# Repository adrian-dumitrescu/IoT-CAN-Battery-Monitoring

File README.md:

# IoT-CAN-Battery-Monitoring

Information about the device is presented in the pCloud_Documentation.pdf file.
- [x] Arduino IDE
- [x] Based on ESP8266
- [x] IoT monitoring with Thingsboard Dashboard
- [x] CAN-BUS

## License
[MIT](https://choosealicense.com/licenses/mit/)

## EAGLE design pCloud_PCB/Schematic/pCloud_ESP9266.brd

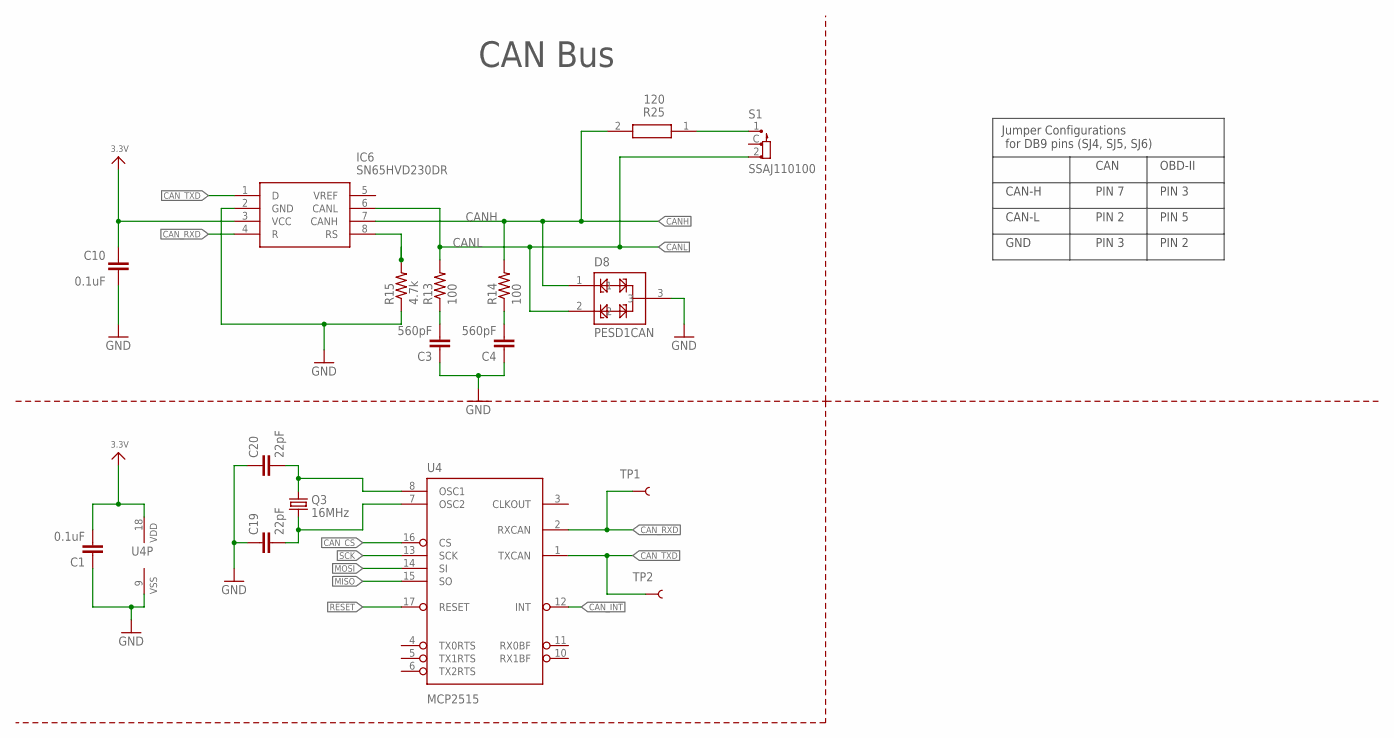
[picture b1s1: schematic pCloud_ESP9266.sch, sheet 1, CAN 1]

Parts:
C1, C10: 0.1uF; 0603
C3, C4: 560pF; 0603
C19, C20: 22pF; 0603
D8: PESD1CAN; SOT23-3
IC6: SN65HVD230DR; SOT127P600X175-8N
Q3: 16MHz; CRYSTAL-SMD-5X3
R13, R14: 100; 0603
R15: 4.7k; 0603
R25: 120; RESC1608X55N
S1: SSAJ110100; SW_SSAJ110100
TP1, TP2: TEST-POINT3X5; PAD.03X.05
U4: MCP2515; SO-18W

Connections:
3.3V: C1.2, C10.2, IC6.3 (VCC), U4.18 (VDD); also elsewhere on the board
CANH: D8.1, IC6.7 (CANH), R14.2, R25.2; also elsewhere on the board
CANL: D8.2, IC6.6 (CANL), R13.2, S1.2; also elsewhere on the board
CAN_CS: U4.16 (CS); also elsewhere on the board
CAN_INT: U4.12 (INT); also elsewhere on the board
CAN_RXD: IC6.4 (R), TP1.P$1, U4.2 (RXCAN)
CAN_TXD: IC6.1 (D), TP2.P$1, U4.1 (TXCAN)
GND: C1.1, C3.1, C4.1, C10.1, C19.1, C20.1, D8.3, IC6.2 (GND), R15.1, U4.9 (VSS); also elsewhere on the board
MISO: U4.15 (SO); also elsewhere on the board
MOSI: U4.14 (SI); also elsewhere on the board
unnamed: C3.2, R13.1
unnamed: C4.2, R14.1
unnamed: R25.1, S1.1
unnamed: IC6.8 (RS), R15.2
unnamed: C20.2, Q3.3 (2), U4.8 (OSC1)
unnamed: C19.2, Q3.1, U4.7 (OSC2)
RESET: U4.17 (RESET); also elsewhere on the board
SCK: U4.13 (SCK); also elsewhere on the board

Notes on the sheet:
CAN Bus
CAN
OBD-II
CAN-H
CAN-L
GND
PIN 5
PIN 2
PIN 3
PIN 7
Jumper Configurations for DB9 pins (SJ4, SJ5, SJ6)

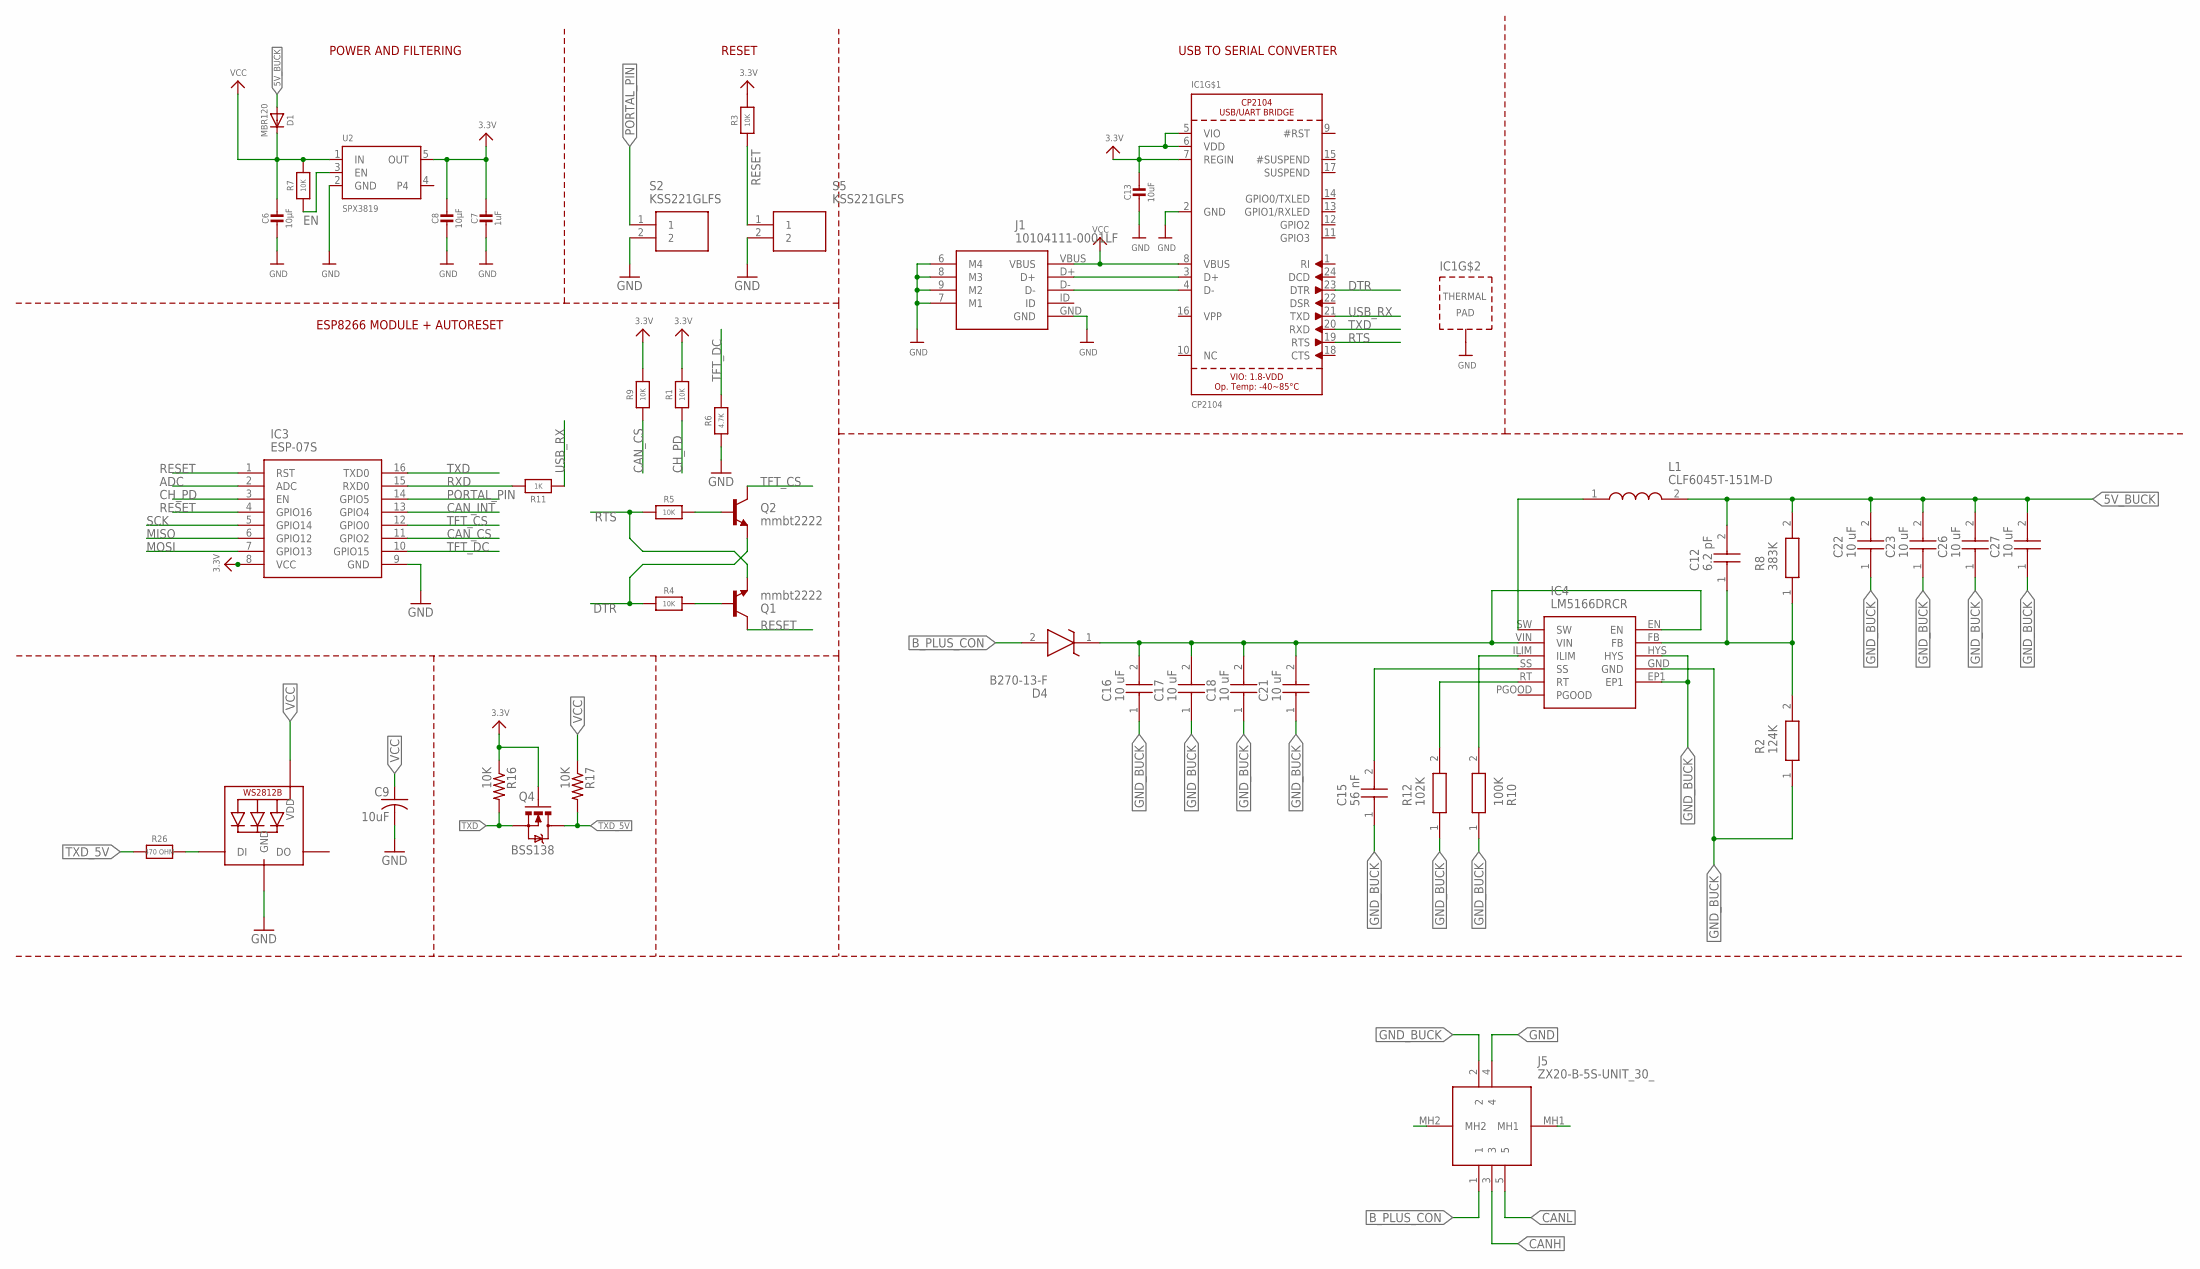
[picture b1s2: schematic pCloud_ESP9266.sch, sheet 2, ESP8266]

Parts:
C6, C8: 10µF; 0805
C7: 1uF; 0603
C9: 10uF; C0805K
C12: 6.2 pF; CAPC1005X55N
C13: 10uF; 0805
C15: 56 nF; CAPC1005X55N
C16, C17, C18, C21, C22, C23, C26, C27: 10 uF; CAPC3225X270N
D1: MBR120; SOD-123
D4: B270-13-F; DIOM5336X250N
IC1: CP2104; QFN24_4MM_SMSC
IC3: ESP-07S; ESP07S
IC4: LM5166DRCR; TPS74901DRCR
J1: 10104111-0001LF; 101041110001LF
J5: ZX20-B-5S-UNIT_30_; ZX20B5SUNIT30
L1: CLF6045T-151M-D; CLF6045T151MD
LED4: WS2812B5050; WS2812B
Q1, Q2: mmbt2222; SOT23-3
Q4: BSS138; SOT23-3
R1, R3, R4, R5, R7, R9, R16, R17: 10K; 0603
R2: 124K; RESC1005X40N
R6: 4.7K; 0603
R8: 383K; RESC1005X40N
R10: 100K; RESC1005X40N
R11: 1K; 0603
R12: 102K; RESC1005X40N
R26: 470 OHM; _0805MP
S2, S5: KSS221GLFS; KSS
U2: SPX3819; SOT23-5

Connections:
3.3V: C7.1, C8.1, C13.1, IC1.5 (VIO), IC1.6 (VDD), IC1.7 (REGIN), IC3.8 (VCC), Q4.1 (G), R1.2, R3.2, R9.2, R16.1, U2.5 (OUT); also elsewhere on the board
5V_BUCK: C12.2, C22.2 (C2), C23.2 (C2), C26.2 (C2), C27.2 (C2), D1.A, L1.2, R8.2
ADC: IC3.2 (ADC)
B_PLUS: C16.2 (C2), C17.2 (C2), C18.2 (C2), C21.2 (C2), D4.1 (K), IC4.EN, IC4.VIN
B_PLUS_CON: D4.2 (A), J5.1
CANH: J5.3; also elsewhere on the board
CANL: J5.5; also elsewhere on the board
CAN_CS: IC3.11 (GPIO2), R9.1; also elsewhere on the board
CAN_INT: IC3.13 (GPIO4); also elsewhere on the board
CH_PD: IC3.3 (EN), R1.1
DTR: IC1.23 (DTR), Q2.2 (E), R4.1
EN: R7.1, U2.3 (EN)
GND: C6.2, C7.2, C8.2, C9.2, C13.2, IC1.2 (GND), IC1.THERM (TP), IC3.9 (GND), J1.6 (M4), J1.7 (M1), J1.8 (M3), J1.9 (M2), J1.GND, J5.4, LED4.3-GND (GND), R6.1, S2.2, S5.2, U2.2 (GND); also elsewhere on the board
GND_BUCK: C15.1, C16.1 (C1), C17.1 (C1), C18.1 (C1), C21.1 (C1), C22.1 (C1), C23.1 (C1), C26.1 (C1), C27.1 (C1), IC4.EP1, IC4.GND, IC4.HYS, J5.2, R2.1, R10.1, R12.1
MISO: IC3.6 (GPIO12); also elsewhere on the board
MOSI: IC3.7 (GPIO13); also elsewhere on the board
unnamed: IC4.SW, L1.1
unnamed: IC4.ILIM, R10.2
unnamed: C12.1, IC4.FB, R2.2, R8.1
unnamed: IC1.3 (D+), J1.D+
unnamed: IC1.4 (D-), J1.D-
unnamed: Q1.1 (B), R4.2
unnamed: Q2.1 (B), R5.2
unnamed: C15.2, IC4.SS
unnamed: IC4.RT, R12.2
unnamed: LED4.4-DIN (DI), R26.2
PORTAL_PIN: IC3.14 (GPIO5), S2.1
RESET: IC3.1 (RST), IC3.4 (GPIO16), Q1.3 (C), R3.1, S5.1; also elsewhere on the board
RTS: IC1.19 (RTS), Q1.2 (E), R5.1
RXD: IC3.15 (RXD0), R11.2
SCK: IC3.5 (GPIO14); also elsewhere on the board
TFT_CS: IC3.12 (GPIO0), Q2.3 (C); also elsewhere on the board
TFT_DC: IC3.10 (GPIO15), R6.2; also elsewhere on the board
TXD: IC1.20 (RXD), IC3.16 (TXD0), Q4.2 (S), R16.2
TXD_5V: Q4.3 (D), R17.2, R26.1
USB_RX: IC1.21 (TXD), R11.1
VCC: C6.1, C9.1, D1.C, IC1.8 (VBUS), J1.VBUS, LED4.1-VDD (VDD), R7.2, R17.1, U2.1 (IN)

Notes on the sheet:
POWER AND FILTERING
RESET
USB TO SERIAL CONVERTER
ESP8266 MODULE + AUTORESET

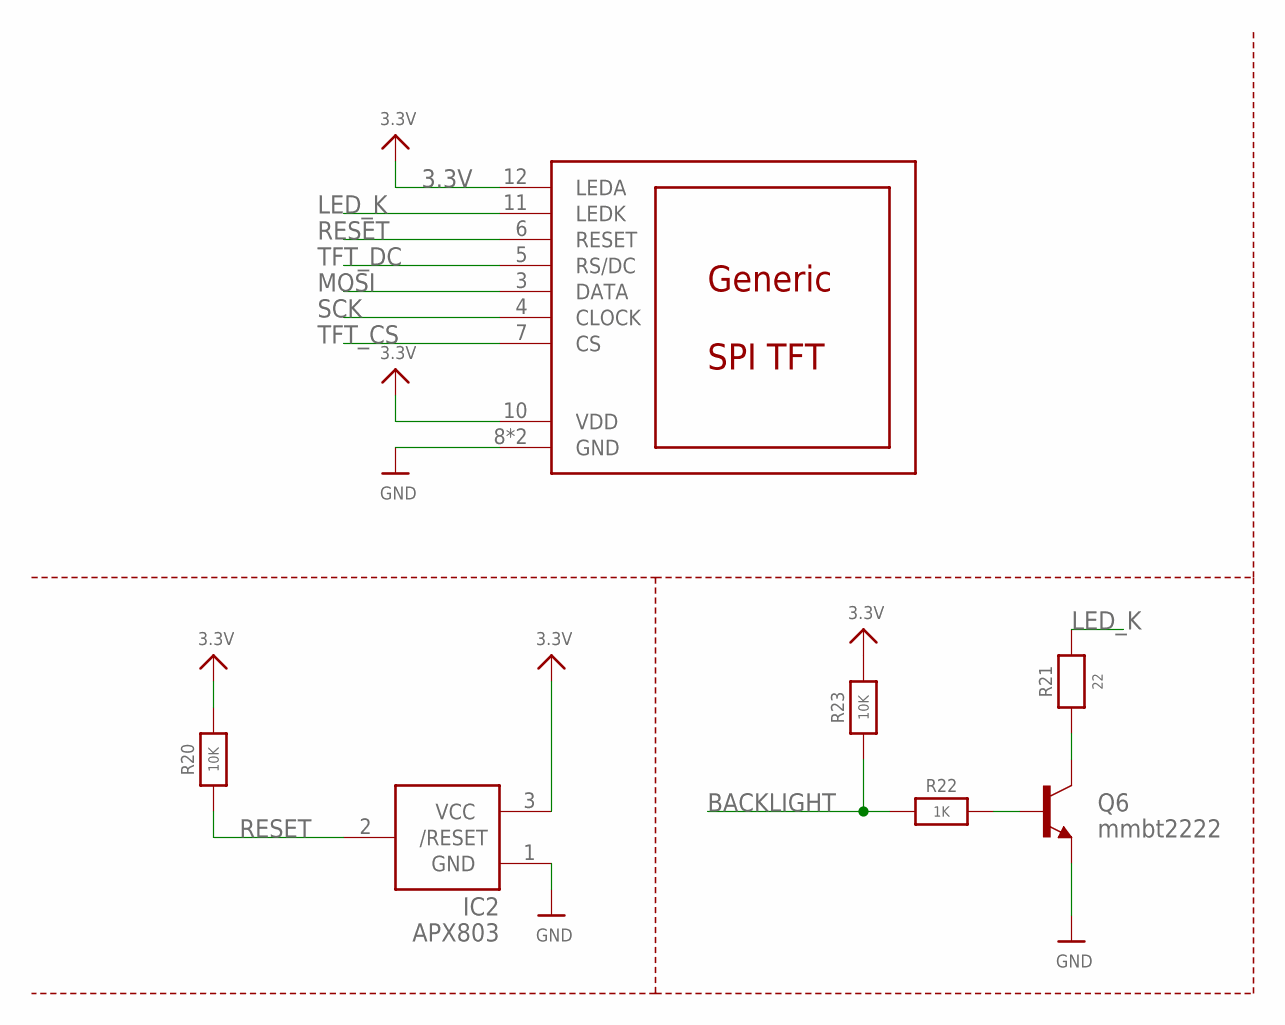
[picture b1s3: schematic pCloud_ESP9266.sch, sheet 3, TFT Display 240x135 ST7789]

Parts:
DISP1: DISP_LCD_GENERIC_SPI_1.14IN_240X135_WRAPUNDER; TFT_1.14IN_240X135_WRAPUNDER
IC2: APX803; SOT23
Q6: mmbt2222; SOT23-3
R20, R23: 10K; 0603
R21: 22; 0603
R22: 1K; 0603

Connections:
3.3V: DISP1.10 (VDD), DISP1.12 (LEDA), IC2.3 (VCC), R20.2, R23.2; also elsewhere on the board
BACKLIGHT: R22.1, R23.1
GND: DISP1.8 (GND), DISP1.13 (GND), IC2.1 (GND), Q6.2 (E); also elsewhere on the board
LED_K: DISP1.11 (LEDK), R21.2
MOSI: DISP1.3 (DATA); also elsewhere on the board
unnamed: Q6.1 (B), R22.2
unnamed: Q6.3 (C), R21.1
RESET: DISP1.6 (RESET), IC2.2 (/RESET), R20.1; also elsewhere on the board
SCK: DISP1.4 (CLOCK); also elsewhere on the board
TFT_CS: DISP1.7 (CS); also elsewhere on the board
TFT_DC: DISP1.5 (RS/DC); also elsewhere on the board

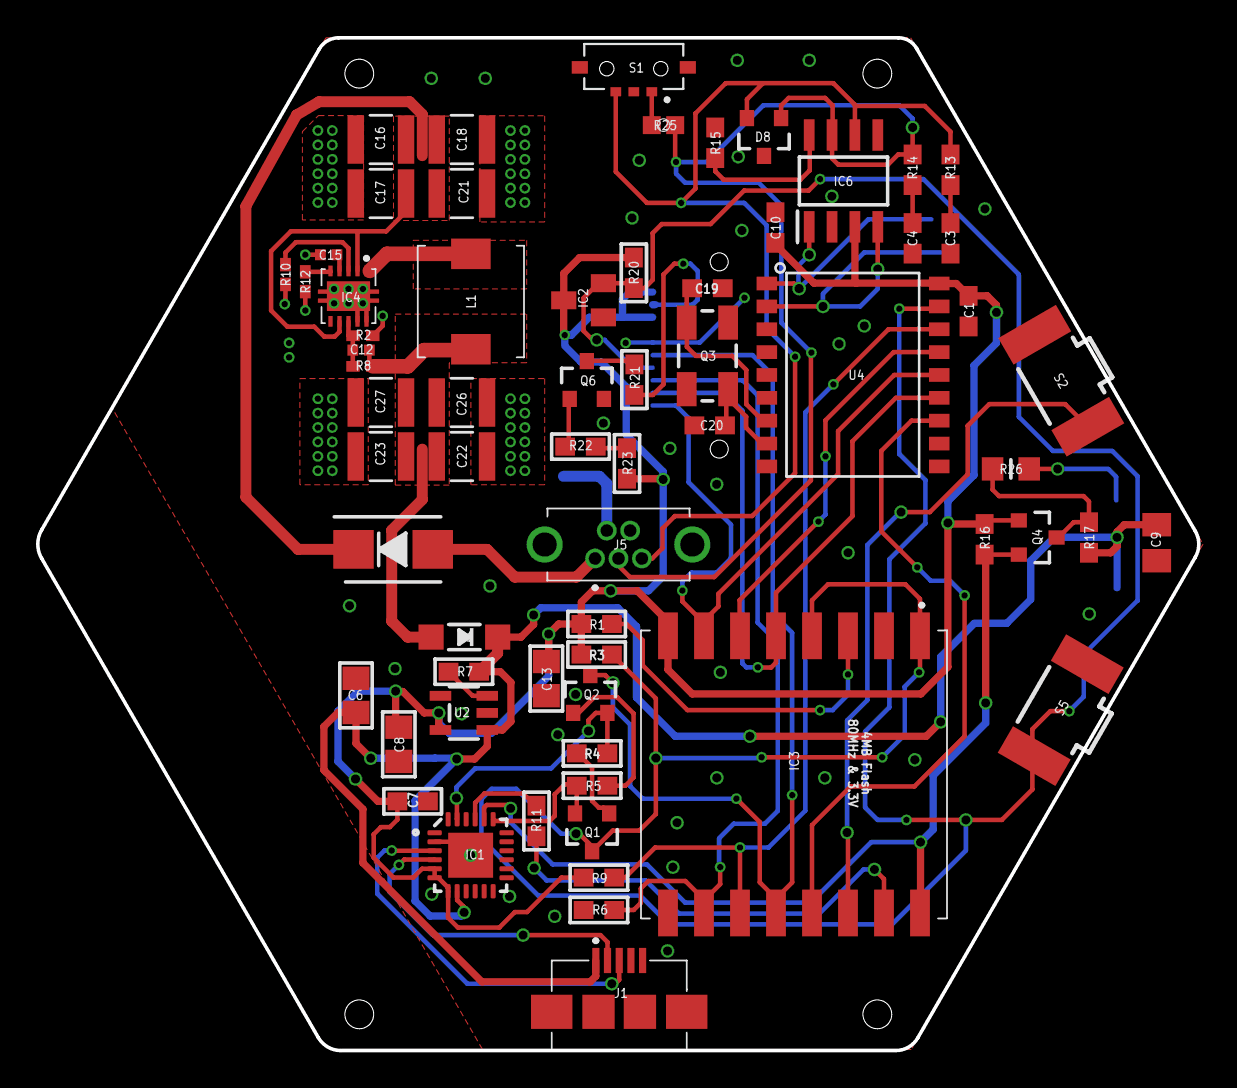
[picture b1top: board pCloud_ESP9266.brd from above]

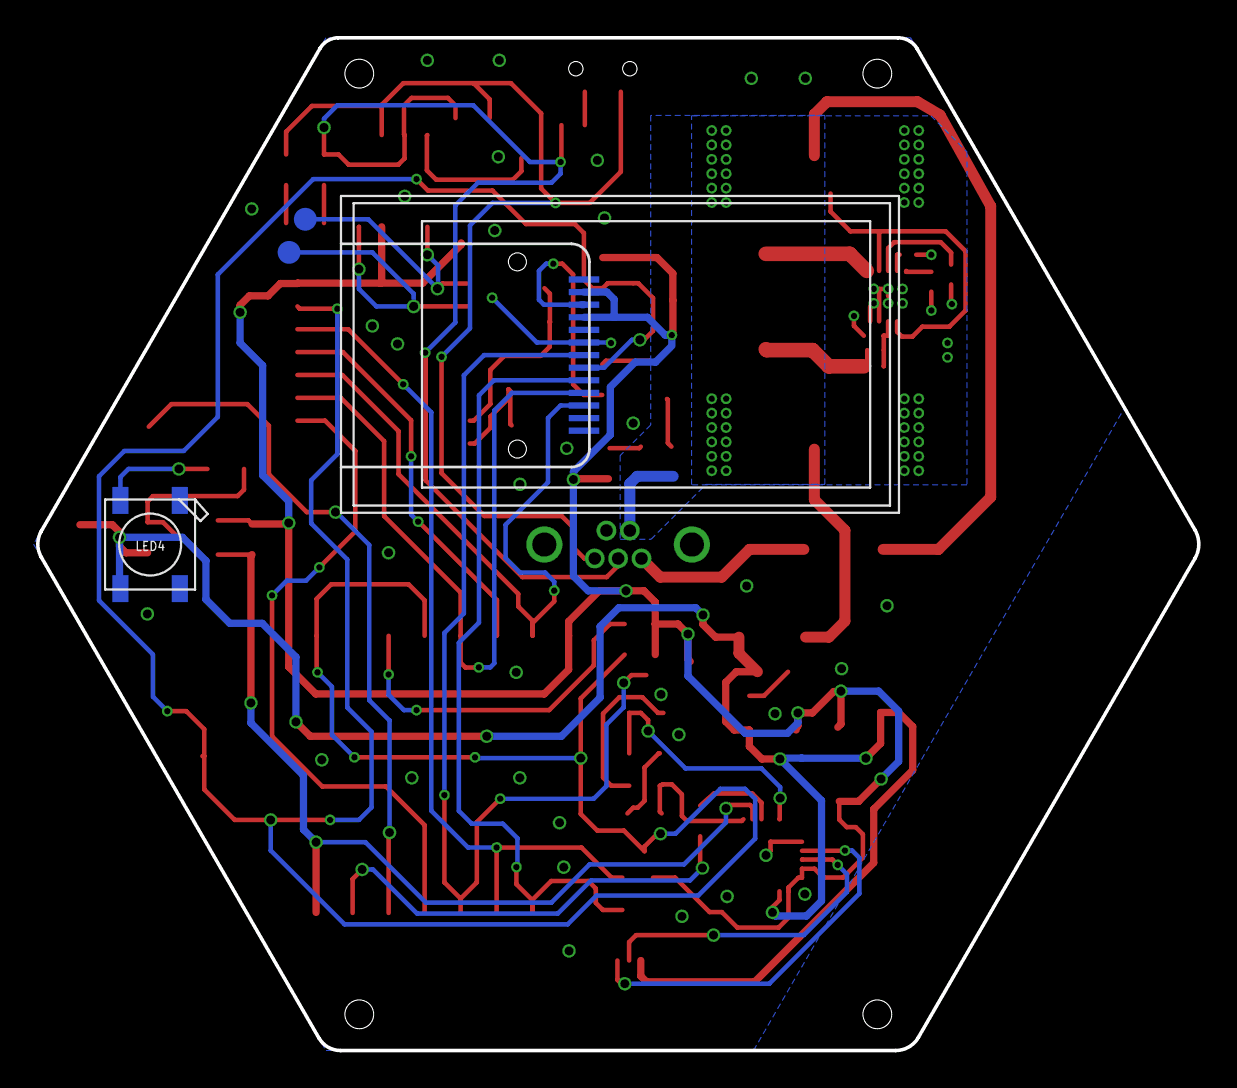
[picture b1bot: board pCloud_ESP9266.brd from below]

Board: 2 copper layers, 64.5 x 56.3 mm, 69 parts (4 on the bottom side), 48 nets.

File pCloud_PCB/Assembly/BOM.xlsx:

QTY | Parts | Description | Value | Footprint (in) | Mounting Style | Manufacturer Part Number | Manufacturer | Supplyer | Supplyer Link | Price/Unit | Price/Total | TOTAL
 | Resistors |  |  |  |  |  |  |  |  |  | 0
1 | R2 | Thick Film Resistors - SMD 1/16watt 124Kohms 1% | 124K | 0402 | SMD | CRCW0402124KFKED | Vishay / Dale | Mouser | Link1 | 0.09 | 0.09 | 49.868999999999986
1 | R8 | Thick Film Resistors - SMD 1/16watt 383Kohms 1% | 383K | 0402 | SMD | CRCW0402383KFKED | Vishay / Dale | Mouser | Link2 | 0.09 | 0.09
1 | R12 | Thick Film Resistors - SMD 1/16watt 102Kohms 1% 100ppm | 102K | 0402 | SMD | CRCW0402102KFKED | Vishay / Dale | Mouser | Link3 | 0.09 | 0.09
1 | R10 | Thick Film Resistors - SMD 1/16watt 100Kohms 1% | 100K | 0402 | SMD | CRCW0402100KFKED | Vishay / Dale | Mouser | Link4 | 0.09 | 0.09
2 | R13, R14 | RES SMD 1/10Watt 100ohms 1% | 100 | 0603 | SMD | CRCW0603100RFKEAC | Vishay / Dale | Mouser | Link5 | 0.09 | 0.18
2 | R16, R17 | RES 0.25watt 10Kohms 1% 100ppm | 10K | 0603 | SMD | RCS060310K0FKEA | Vishay / Dale | Mouser | Link6 | 0.14000000000000001 | 0.28000000000000003
8 | R5, R1, R3, R4, R7, R9, R20, R23 | Thick Film Resistors - SMD 10K OHM 1% 1/4W TC100 | 10K | 0603 | SMD | CMP0603AFX-1002ELF | Bourns | Mouser | Link7 | 0.09 | 0.72
1 | R25 | Thick Film Resistors - SMD 120 Ohm | 120 | 0603 | SMD | RC0603JR-7W120RL | Yageo | Mouser | Link8 | 0.09 | 0.09
1 | R21 | Thick Film Resistors - SMD 1/10Watt 22ohms 5% Commercial Use | 22 | 0603 | SMD | CRCW060322R0JNEAC | Vishay / Dale | Mouser | Link9 | 0.09 | 0.09
2 | R11, R22 | Thin Film Resistors - SMD 1K ohm 1% 1/10W | 1 K | 0603 | SMD | RT0603FRE071KL | Yageo | Mouser | Link10 | 0.09 | 0.18
2 | R15, R6 | RES 4.7Kohms 1% | 4.7K | 0603 | SMD | ERJ-3EKF4701V | Panasonic | Mouser | Link11 | 0.1 | 0.2
1 | R26 | Thick Film Resistors - SMD 1/8Watt 470ohms 1% Commercial Use | 470 | 0805 | SMD | CRCW0805470RFKEAC | Vishay / Dale | Mouser | Link12 | 0.09 | 0.09
 | Capacitors |  |  |  |  |  |  |  |  |  | 0
1 | C12 | Multilayer Ceramic Capacitors MLCC - SMD/SMT 0402 6.2pF 50volts C0G +/-0.25pF | 6.2 pF | 0402 | SMD | GRM1555C1H6R2CA01D | Murata Electronics | Mouser | link13 | 0.09 | 0.09
1 | C15 | Multilayer Ceramic Capacitors MLCC - SMD/SMT 0.056uF 16Volts 10% | 56 nF | 0402 | SMD | GRM155R71C563KA88D | Murata Electronics | Mouser | Link14 | 8.5000000000000006E-2 | 8.5000000000000006E-2
8 | C16, C17, C18, C21, C22, C23, C26, C27 | Multilayer Ceramic Capacitors MLCC - SMD/SMT 100Vdc 10uF 10% 1210/2502 | 10 uF | 1210 | SMD | GRM32EC72A106KE05L | Murata Electronics | Mouser | Link15 | 1.17 | 9.36
2 | C1, C10 | CAP 0.1uF 25V 20% 0603 | 0.1 uF | 0603 | SMD | CC0603ZRY5V8BB104 | Yageo | Mouser | Link16 | 0.09 | 0.18
4 | C13, C6, C8, C9 | CAP 10UF 25V 10% 0805 | 10 uF | 0805 | SMD | GRM21BR61E106KA73K | Murata Electronics | Mouser | Link17 | 0.23 | 0.92
2 | C3, C4 | CAP 560pF +-5% 50V | 560 pF | 0603 | SMD | 0603N561J500CT | Walsin | Mouser | Link18 | 0.11 | 0.22
2 | C19, C20 | Multilayer Ceramic Capacitors MLCC - SMD/SMT WCAP-CSGP 22pF 0603 5% 50V MLCC | 22 pF | 0603 | SMD | 885012006053 | Wurth Elektronik | Mouser | Link19 | 0.09 | 0.18
1 | C7 | CAP 1.0uF 25V X5R 10% | 1 uF | 0603 | SMD | CC0603KRX5R8BB105 | Yageo | Mouser | Link20 | 0.09 | 0.09
 | Other |  |  |  |  |  |  |  |  |  | 0
1 | X4 | USB Connectors 5P Quick Connect MicroUSB TypeAB Rcpt | - | - | SMD | 10104111-0001LF | Amphenol FCI | Mouser | Link21 | 0.6 | 0.6
1 | IC2 | Supervisory Circuits 2.63V, 50ms MPU Reset Circuit | - | SOT-23-3 | SMD | APX803S05-26SA-7 or APX803S05-29SA-7 | Diodes Incorporated | Mouser | Link22 | 0.31 | 0.31
1 | D4 | Schottky Diodes & Rectifiers 2.0A 70V | - | SMB | SMD | B270-13-F | Diodes Incorporated | Mouser | Link23 | 0.34 | 0.34
1 | Q4 | MOSFET SOT-23 N-CH LOGIC | - | SOT-23-3 | SMD | BSS138 | ON Semiconductor / Fairchild | Mouser | Link24 | 0.22 | 0.22
1 | IC1 | I/O Controller Interface IC USB to UART Bridge QFN24 | - | QFN-24 | SMD | CP2104-F03-GMR | Silicon Labs | Mouser | Link25 | 1.4 | 1.4
1 | IC3 | ESP8266 WiFi 802.11b/g/n 160Mbits | - | - | SMD | ESP-07S | RF Solutions | Mouser | Link26 | 8.5399999999999991 | 8.5399999999999991
2 | S2, S5 | Tactile Switches SPST NO-G LEAD 200g | - | - | SMD | KSS221GLFS | C&K | Mouser | Link27 | 0.64 | 1.28
1 | D5 | Schottky Diodes & Rectifiers 1A 20V | - | SOD-123FL | SMD | MBR120VLSFT1G | ON Semiconductor | Mouser | Link28 | 0.37 | 0.37
1 | U4 | CAN Interface IC W/ SPI Interface |  | SOIC-18 | SMD | MCP2515-I/SO | Microchip Technology | Mouser | Link29 | 1.54 | 1.54
3 | Q1, Q2, Q6 | Bipolar Transistors - BJT SS SOT23 GP XSTR NPN 30V | - | SOT-23-3 | SMD | MMBT2222LT1G | ON Semiconductor | Mouser | Link30 | 0.11 | 0.33
1 | D8 | TVS Diodes CAN BUS ESD PROTECT | - | - | SMD | PESD1CAN,215 | Nexperia | Mouser | Link31 | 0.41 | 0.41
1 | IC6 | CAN Interface IC STANDBY MODE |  | SOIC-8 | SMD | SN65HVD230DR | Texas Instruments | Mouser | Link32 | 1.85 | 1.85
1 | U2 | LDO Voltage Regulators 500mA | - | SOT-23-5 | SMD | SPX3819M5-L-3-3/TR | MaxLinear | Mouser | Link33 | 0.63 | 0.63
1 | S1 | Slide Switches slide switch with location lug | - | - | SMD | SSAJ110100 | Alps Alpine | Mouser | Link34 | 1.51 | 1.51
1 | LED4 | SK6812 LEDs | - | 5050 | SMD | 2760 | Adafruit | Mouser | Link35 | 0.504 | 0.504
1 | D1 | DIODE-SCHOTTKYSOD-123 | - | SOD-123FL | SMD | MBR120ESFT3G | ON Semiconductor | Mouser | Link36 | 0.32 | 0.32
1 | L1 | CLF6045T-151M-D | 150uH | - | SMD | CLF6045T-151M-D or CLF6045T-101M-D | TDK | Mouser | Link38 | 1.1200000000000001 | 1.1200000000000001
1 | IC4 | Switching Voltage Regulators | - | VSON-10 | SMD | LM5166DRCR | Texas Instruments | Mouser | Link39 | 2.87 | 2.87
1 | Q3 | Crystal SMD 16MHz | 16Mhz | - | SMD | COM-00094 | SparkFun | Mouser | Link40 | 1.35 | 1.35
EXTERNAL COMPONENTS (NOT TO BE MOUNTED / BOUGHT):
QTY | Parts | Description | Value | Footprint (in) | Mounting Style | Manufacturer Part Number | Manufacturer | Supplyer | Supplyer Link | Price/Unit | Price/Total | TOTAL
1 | DISP1 | 1.14 inch IPS HD TFT LCD display with 135x240 dots | - | - | SMD | ER-TFT1.14-1 | EastRising | buydisplay | Link41 | 2.6 | 2.6
1 | CON | USB Connectors MICRO B PLUG ASBY VERT PCB | - | - | TH | ZX20-B-5S-UNIT(30) | Hirose Connector | Mouser | Link42 | 0.74 | 0.74
1 | CON-Metal | USB Connectors MICRO B PLUG SHIELD FOR ZX20 VERT TH | - | - | TH | ZX20-B-SLDC | Hirose Connector | Mouser | Link43 | 0.22 | 0.22
1 | Antenna | 2.4G 5.8G dual band FPC Antenna 31*5.5 cm | - | - | Snap In |  | - | Alibaba |  | 0.4 | 0.4
1 | Panel CON | USB Connectors RUGGED MICRO AB VERTICAL | - | - | Panel | MUSBK55230 | Amphenol Commercial Products | Mouser | Link44 | 7.1 | 7.1

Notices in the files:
parts and their libraries:
microbuilder: This work is placed in the public domain, and may be freely used for commercial and non-commercial work with the following conditions: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
SparkFun: Licensing: CC v3.0 Share-Alike You are welcome to use this library for commercial purposes.
